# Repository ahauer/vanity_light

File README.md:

# vanity_light
Vanity Table LED Lighting

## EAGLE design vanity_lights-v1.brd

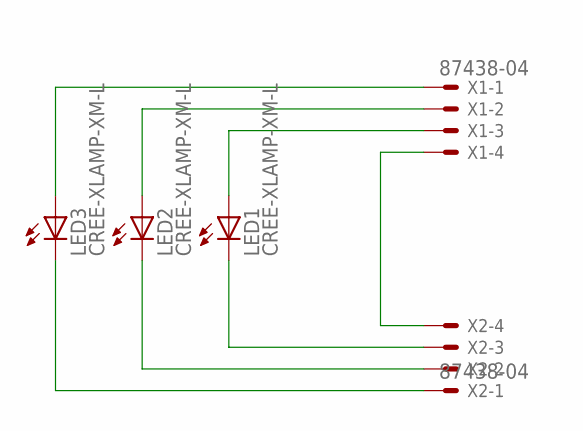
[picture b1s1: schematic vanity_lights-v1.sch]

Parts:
LED1, LED2, LED3: CREE-XLAMP-XM-L
X1, X2: 87438-04

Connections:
unnamed: LED3.A, LED3.A@1 (A), X1.1
unnamed: LED2.A, LED2.A@1 (A), X1.2
unnamed: LED1.A, LED1.A@1 (A), X1.3
unnamed: LED3.C, LED3.C@1 (C), X2.1
unnamed: LED2.C, LED2.C@1 (C), X2.2
unnamed: LED1.C, LED1.C@1 (C), X2.3
unnamed: X1.4, X2.4

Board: 2 copper layers, 5 parts (0 on the bottom side), 7 nets, no tracks yet.
